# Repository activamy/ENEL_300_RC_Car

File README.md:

# ENEL_300_RC_Car
ENEL 300 Design Project 2026

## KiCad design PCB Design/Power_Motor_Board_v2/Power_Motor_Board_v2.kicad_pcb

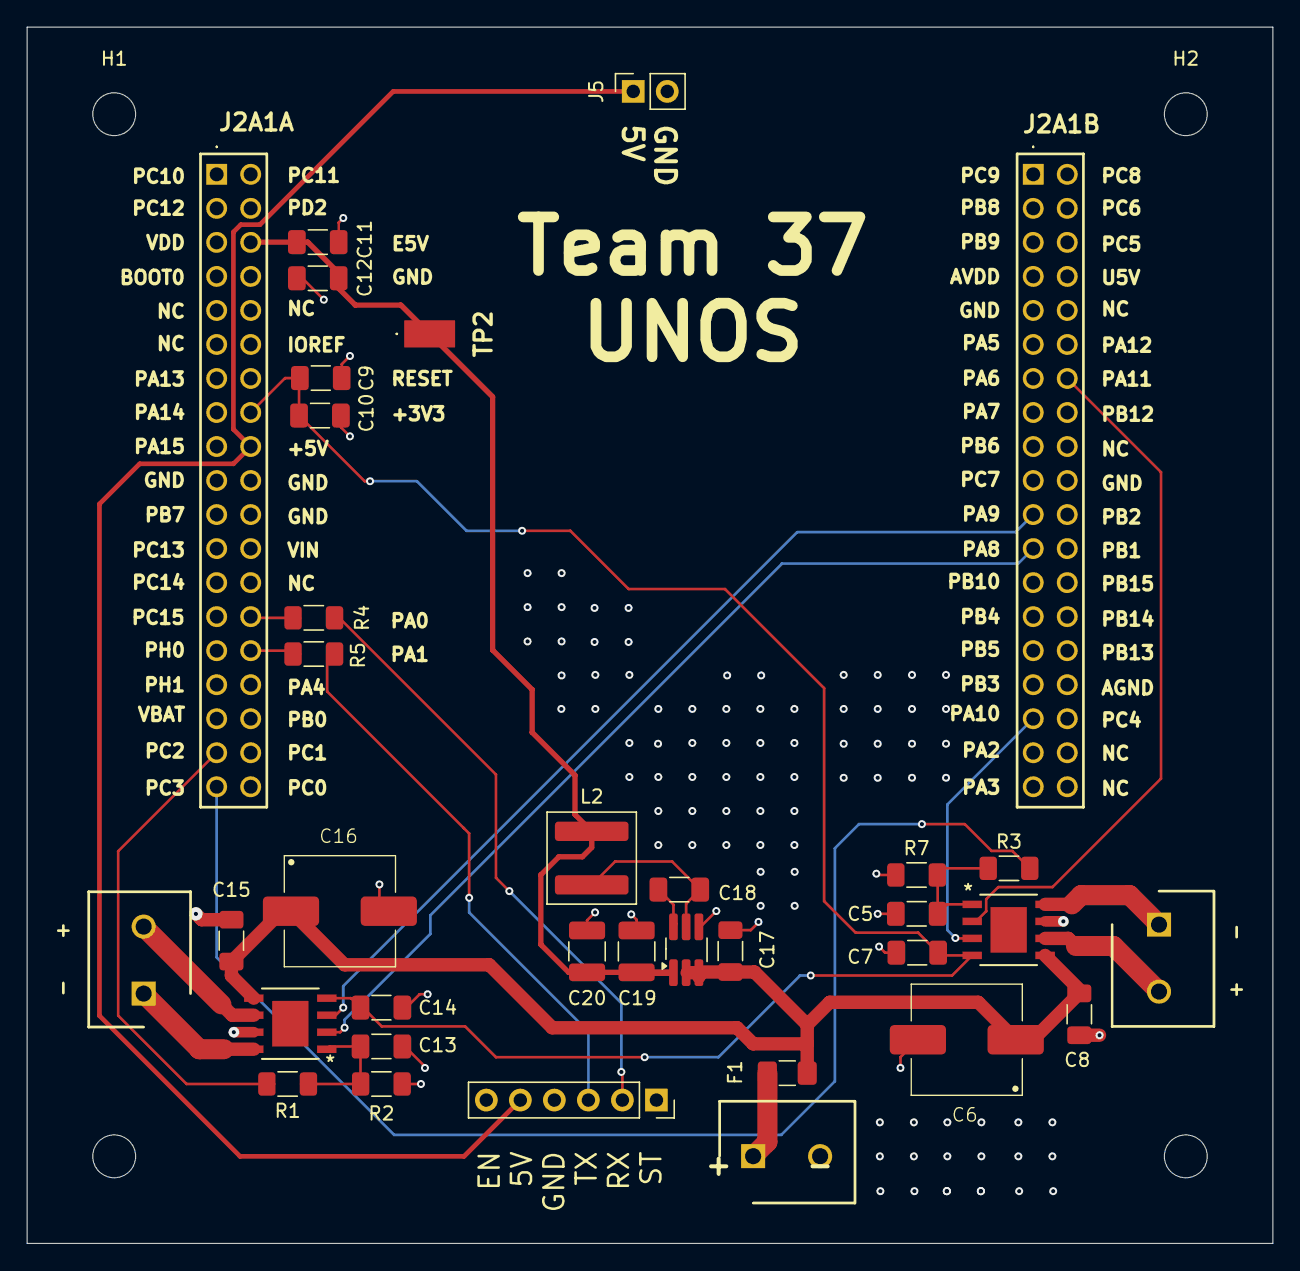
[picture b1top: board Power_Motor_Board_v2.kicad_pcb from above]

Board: 2 copper layers, 93.0 x 90.8 mm, 38 parts (0 on the bottom side), 24 nets.

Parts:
C5, C13: 10nF; C_1206_3216Metric_Pad1.33x1.80mm_HandSolder
C6, C16: 180uF; A768KE187M1ELAE029
C7, C8, C9, C11, C14, C15, C18: 0.1uF; C_1206_3216Metric_Pad1.33x1.80mm_HandSolder
C10, C12: 1uF; C_1206_3216Metric_Pad1.33x1.80mm_HandSolder
C17: 10uF; C_1206_3216Metric_Pad1.33x1.80mm_HandSolder
C19, C20: 22uF; C_1210_3225Metric_Pad1.33x2.70mm_HandSolder
F1: 4A; Fuse_1206_3216Metric_Pad1.42x1.75mm_HandSolder
H1, H2, H3, H4: MountingHole; MountingHole_3.2mm_M3
IC1, IC3: DRV8251ADDAR; SOIC-8-DDA-DRV8231_TEX
IC4: AP63205WU-7; TSOT-23-6_HandSoldering
J1, J2, J3: 691137710002; SHDR2W70P0X500_1X2_1000X750X1150P
J2A1: SSW-119-01-T-D; STM_Nucleo_Morpho_x2_Footprint
J4: Conn_01x06; PinSocket_1x06_P2.54mm_Vertical
J5: Conn_01x02_Socket; PinSocket_1x02_P2.54mm_Vertical
L2: 4.7uH; L_Wuerth_XHMI-6060
R1, R3, R4, R5: 0Ω; R_1206_3216Metric_Pad1.30x1.75mm_HandSolder
R2, R7: 750Ω; R_1206_3216Metric_Pad1.30x1.75mm_HandSolder
TP2: 5019

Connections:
5V_out: J2A1.A18 (+5V), J4.5, J5.1
+3V3: C7.1, C9.1, C10.1, C14.1, IC1.4 (VREF), IC3.4 (VREF), J2A1.A16 (+3V3)
+5V: C11.1, C12.1, C19.2, C20.2, IC4.1 (FB), J2A1.A6 (E5V), L2.2, TP2.1
+Vbatt: C6.1, C8.1, C15.1, C16.1, C17.1, F1.2, IC1.5 (VM), IC3.5 (VM), IC4.2 (EN), IC4.3 (VIN)
/+OUT_1: IC1.6 (OUT1), J3.2
/+OUT_2: IC3.6 (OUT1), J2.2
/-OUT_1: IC1.8 (OUT2), J3.1
/-OUT_2: IC3.8 (OUT2), J2.1
/BT_RX: J2A1.A28 (PA0), R4.1
/BT_TX: J2A1.A30 (PA1), R5.1
/IN1_MTR1: IC1.3 (IN1), J2A1.B21 (PA9)
/IN1_MTR2: IC3.3 (IN1), J2A1.B33 (PA10)
/IN2-MTR1: IC1.2 (IN2), J2A1.B23 (PA8)
/IN2_MTR2: IC3.2 (IN2), J2A1.B14 (PA11)
/I_MTR1: J2A1.A35 (PC2), R1.1
/I_MTR2: J2A1.A37 (PC3), R3.1
GND: C5.2, C6.2, C7.2, C8.2, C9.2, C10.2, C11.2, C12.2, C13.2, C14.2, C15.2, C16.2, C17.2, C19.1, C20.1, IC1.7 (GND_1), IC3.7 (GND_1), IC4.4 (GND), J1.2, J2A1.A8 (GND), J2A1.A19 (GND), J2A1.A20 (GND), J2A1.A22 (GND), J2A1.B9 (GND), J2A1.B20 (GND), J4.4, J5.2, R2.2, R7.2
unnamed: F1.1, J1.1
unnamed: C13.1, IC1.1 (IPROPI), R1.2, R2.1
unnamed: C5.1, IC3.1 (IPROPI), R3.2, R7.1
unnamed: C18.2, IC4.6 (BST)
unnamed: C18.1, IC4.5 (SW), L2.1
unnamed: J4.2, R4.2
unnamed: J4.3, R5.2

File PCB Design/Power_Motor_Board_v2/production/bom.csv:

Designator,Footprint,Quantity,Value,LCSC Part #
"C10, C12",1206,2,1uF,
"C11, C14, C15, C18, C7, C8, C9",1206,7,0.1uF,
"C13, C5",1206,2,10nF,
"C16, C6",A768KE187M1ELAE029,2,180uF,
C17,1206,1,10uF,
"C19, C20",1210,2,22uF,
F1,1206,1,4A,
"IC1, IC3",SOIC-8-DDA-DRV8231_TEX,2,DRV8251ADDAR,
IC4,TSOT-23-6_HandSoldering,1,AP63205WU-7,
J2A1,STM_Nucleo_Morpho_x2_Footprint,1,SSW-119-01-T-D,
J4,PinSocket_1x06_P2.54mm_Vertical,1,Conn_01x06,
J5,PinSocket_1x02_P2.54mm_Vertical,1,Conn_01x02_Socket,
L2,L_Wuerth_XHMI-6060,1,4.7uH,
"R1, R3, R4, R5",1206,4,0Ω,
"R2, R7",1206,2,750Ω,

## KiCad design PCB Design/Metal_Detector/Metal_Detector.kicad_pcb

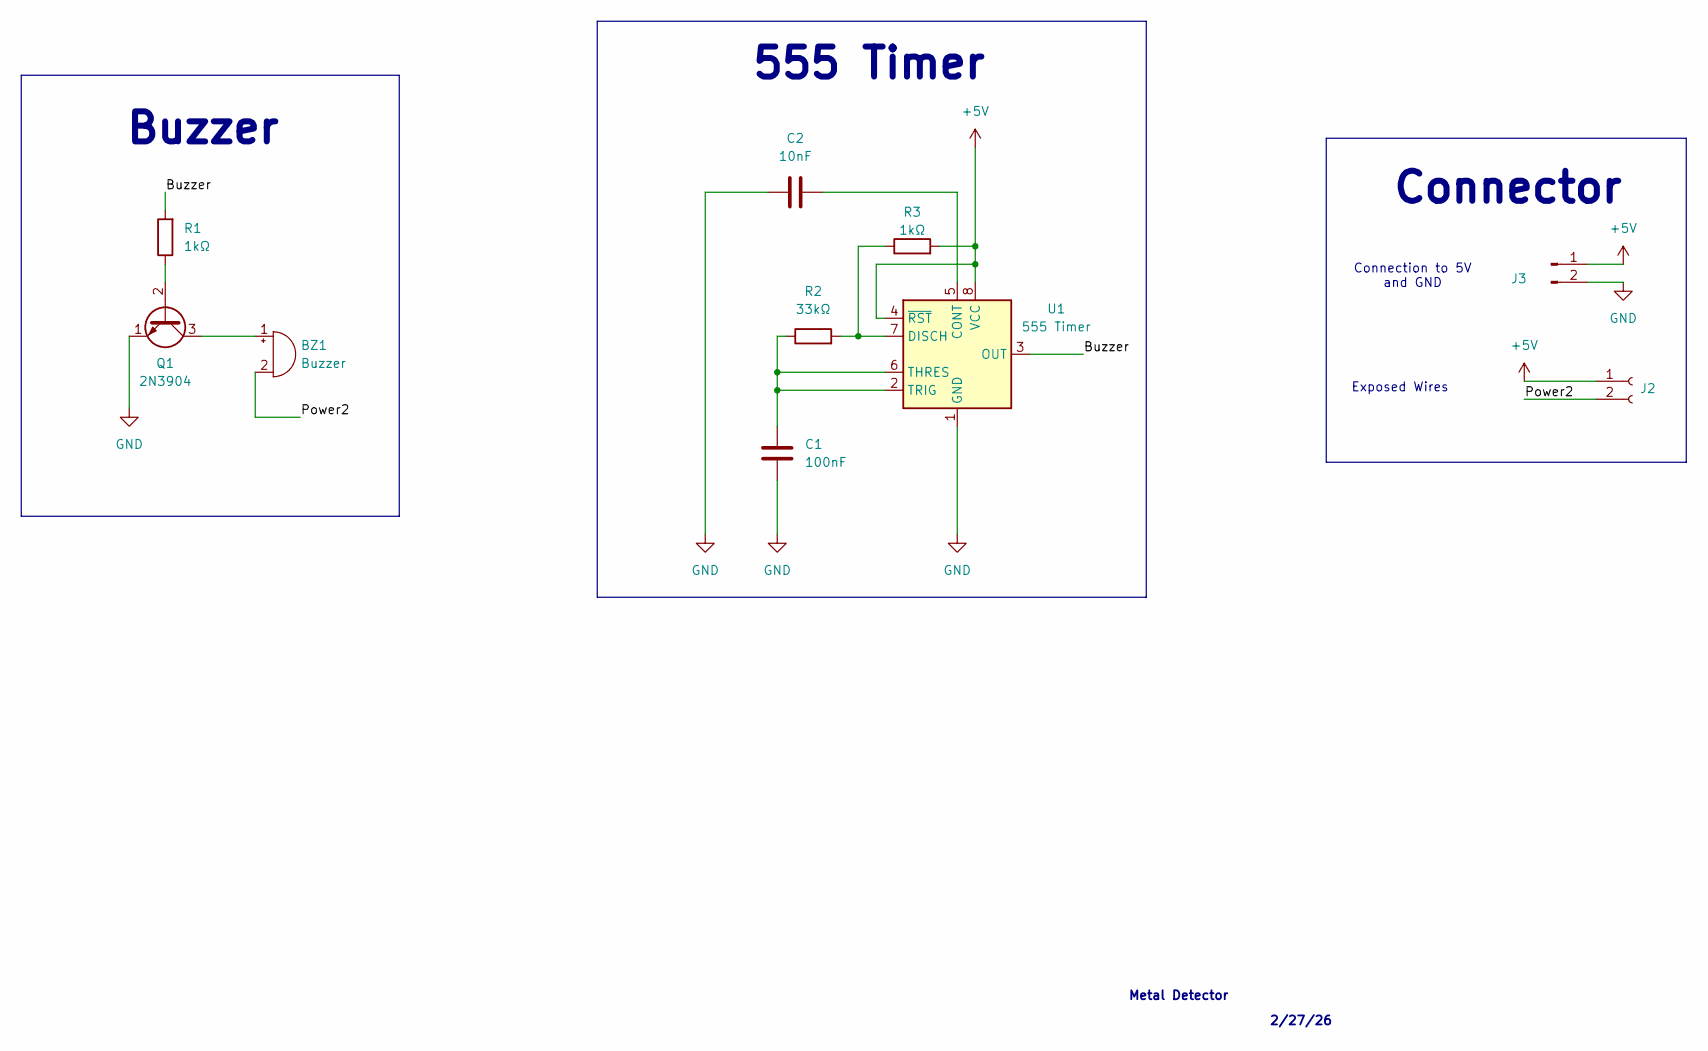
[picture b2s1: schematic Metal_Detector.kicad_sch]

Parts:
BZ1: Buzzer; Buzzer_12x9.5RM7.6
C1: 100nF; C_0805_2012Metric_Pad1.18x1.45mm_HandSolder
C2: 10nF; C_1206_3216Metric_Pad1.33x1.80mm_HandSolder
J2: Conn_01x02_Socket; PinSocket_1x02_P2.54mm_Vertical
J3: Conn_01x02_Pin; PinHeader_1x02_P2.54mm_Vertical
Q1: 2N3904; TO-92L_Inline
R1, R3: 1kΩ; R_1206_3216Metric_Pad1.30x1.75mm_HandSolder
R2: 33kΩ; R_1206_3216Metric_Pad1.30x1.75mm_HandSolder
U1: 555 Timer; SOIC-8_3.9x4.9mm_P1.27mm

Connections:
+5V: J2.1, J3.1, R3.2, U1.4 (~RST), U1.8 (VCC)
/Buzzer: R1.2, U1.3 (OUT)
/Power2: BZ1.2 (-), J2.2
GND: C1.2, C2.1, J3.2, Q1.1 (E), U1.1 (GND)
unnamed: BZ1.1 (+), Q1.3 (C)
unnamed: Q1.2 (B), R1.1
unnamed: C2.2, U1.5 (CONT)
unnamed: R2.2, R3.1, U1.7 (DISCH)
unnamed: C1.1, R2.1, U1.2 (TRIG), U1.6 (THRES)

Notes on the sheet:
Connector
Metal Detector
Buzzer
555 Timer
Exposed Wires
2/27/26
Connection to 5V and GND

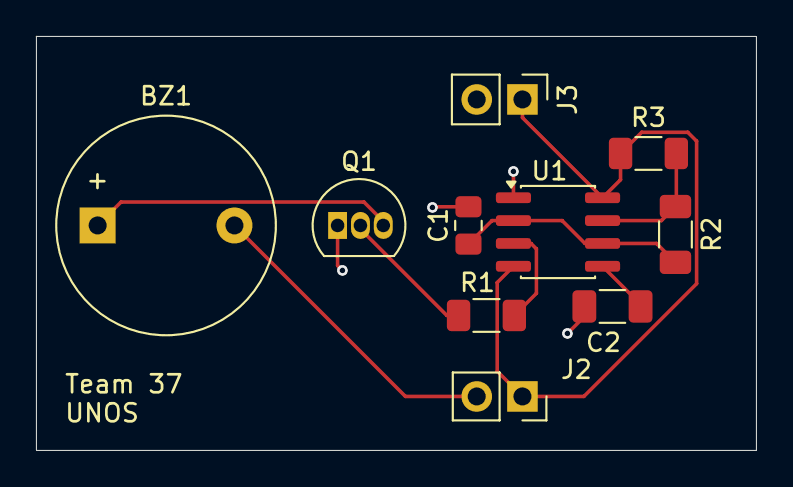
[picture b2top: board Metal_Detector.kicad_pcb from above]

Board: 2 copper layers, 40.0 x 23.0 mm, 10 parts (0 on the bottom side), 9 nets.

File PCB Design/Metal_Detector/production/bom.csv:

Designator,Footprint,Quantity,Value,LCSC Part #
C1,0805,1,100nF,
C2,1206,1,10nF,
"R1, R3",1206,2,1kΩ,
R2,1206,1,33kΩ,

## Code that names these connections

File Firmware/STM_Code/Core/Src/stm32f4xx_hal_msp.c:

/* USER CODE BEGIN Header */
/**
  ******************************************************************************
  * @file         stm32f4xx_hal_msp.c
  * @brief        This file provides code for the MSP Initialization
  *               and de-Initialization codes.
  ******************************************************************************
  * @attention
  *
  * Copyright (c) 2026 STMicroelectronics.
  * All rights reserved.
  *
  * This software is licensed under terms that can be found in the LICENSE file
  * in the root directory of this software component.
  * If no LICENSE file comes with this software, it is provided AS-IS.
  *
  ******************************************************************************
  */
/* USER CODE END Header */

/* Includes ------------------------------------------------------------------*/
#include "main.h"
/* USER CODE BEGIN Includes */

/* USER CODE END Includes */

/* Private typedef -----------------------------------------------------------*/
/* USER CODE BEGIN TD */

/* USER CODE END TD */

/* Private define ------------------------------------------------------------*/
/* USER CODE BEGIN Define */

/* USER CODE END Define */

/* Private macro -------------------------------------------------------------*/
/* USER CODE BEGIN Macro */

/* USER CODE END Macro */

/* Private variables ---------------------------------------------------------*/
/* USER CODE BEGIN PV */

/* USER CODE END PV */

/* Private function prototypes -----------------------------------------------*/
/* USER CODE BEGIN PFP */

/* USER CODE END PFP */

/* External functions --------------------------------------------------------*/
/* USER CODE BEGIN ExternalFunctions */

/* USER CODE END ExternalFunctions */

/* USER CODE BEGIN 0 */

/* USER CODE END 0 */

void HAL_TIM_MspPostInit(TIM_HandleTypeDef *htim);
                    /**
  * Initializes the Global MSP.
  */
void HAL_MspInit(void)
{

  /* USER CODE BEGIN MspInit 0 */

  /* USER CODE END MspInit 0 */

  __HAL_RCC_SYSCFG_CLK_ENABLE();
  __HAL_RCC_PWR_CLK_ENABLE();

  HAL_NVIC_SetPriorityGrouping(NVIC_PRIORITYGROUP_0);

  /* System interrupt init*/

  /* USER CODE BEGIN MspInit 1 */

  /* USER CODE END MspInit 1 */
}

/**
  * @brief ADC MSP Initialization
  * This function configures the hardware resources used in this example
  * @param hadc: ADC handle pointer
  * @retval None
  */
void HAL_ADC_MspInit(ADC_HandleTypeDef* hadc)
{
  GPIO_InitTypeDef GPIO_InitStruct = {0};
  if(hadc->Instance==ADC1)
  {
    /* USER CODE BEGIN ADC1_MspInit 0 */

    /* USER CODE END ADC1_MspInit 0 */
    /* Peripheral clock enable */
    __HAL_RCC_ADC1_CLK_ENABLE();

    __HAL_RCC_GPIOC_CLK_ENABLE();
    /**ADC1 GPIO Configuration
    PC2     ------> ADC1_IN12
    PC3     ------> ADC1_IN13
    */
    GPIO_InitStruct.Pin = GPIO_PIN_2|GPIO_PIN_3;
    GPIO_InitStruct.Mode = GPIO_MODE_ANALOG;
    GPIO_InitStruct.Pull = GPIO_NOPULL;
    HAL_GPIO_Init(GPIOC, &GPIO_InitStruct);

    /* USER CODE BEGIN ADC1_MspInit 1 */

    /* USER CODE END ADC1_MspInit 1 */

  }

}

/**
  * @brief ADC MSP De-Initialization
  * This function freeze the hardware resources used in this example
  * @param hadc: ADC handle pointer
  * @retval None
  */
void HAL_ADC_MspDeInit(ADC_HandleTypeDef* hadc)
{
  if(hadc->Instance==ADC1)
  {
    /* USER CODE BEGIN ADC1_MspDeInit 0 */

    /* USER CODE END ADC1_MspDeInit 0 */
    /* Peripheral clock disable */
    __HAL_RCC_ADC1_CLK_DISABLE();

    /**ADC1 GPIO Configuration
    PC2     ------> ADC1_IN12
    PC3     ------> ADC1_IN13
    */
    HAL_GPIO_DeInit(GPIOC, GPIO_PIN_2|GPIO_PIN_3);

    /* USER CODE BEGIN ADC1_MspDeInit 1 */

    /* USER CODE END ADC1_MspDeInit 1 */
  }

}

/**
  * @brief TIM_PWM MSP Initialization
  * This function configures the hardware resources used in this example
  * @param htim_pwm: TIM_PWM handle pointer
  * @retval None
  */
void HAL_TIM_PWM_MspInit(TIM_HandleTypeDef* htim_pwm)
{
  if(htim_pwm->Instance==TIM1)
  {
    /* USER CODE BEGIN TIM1_MspInit 0 */

    /* USER CODE END TIM1_MspInit 0 */
    /* Peripheral clock enable */
    __HAL_RCC_TIM1_CLK_ENABLE();
    /* USER CODE BEGIN TIM1_MspInit 1 */

    /* USER CODE END TIM1_MspInit 1 */

  }

}

void HAL_TIM_MspPostInit(TIM_HandleTypeDef* htim)
{
  GPIO_InitTypeDef GPIO_InitStruct = {0};
  if(htim->Instance==TIM1)
  {
    /* USER CODE BEGIN TIM1_MspPostInit 0 */

    /* USER CODE END TIM1_MspPostInit 0 */

    __HAL_RCC_GPIOA_CLK_ENABLE();
    /**TIM1 GPIO Configuration
    PA8     ------> TIM1_CH1
    PA9     ------> TIM1_CH2
    PA10     ------> TIM1_CH3
    PA11     ------> TIM1_CH4
    */
    GPIO_InitStruct.Pin = GPIO_PIN_8|GPIO_PIN_9|GPIO_PIN_10|GPIO_PIN_11;
    GPIO_InitStruct.Mode = GPIO_MODE_AF_PP;
    GPIO_InitStruct.Pull = GPIO_NOPULL;
    GPIO_InitStruct.Speed = GPIO_SPEED_FREQ_LOW;
    GPIO_InitStruct.Alternate = GPIO_AF1_TIM1;
    HAL_GPIO_Init(GPIOA, &GPIO_InitStruct);

    /* USER CODE BEGIN TIM1_MspPostInit 1 */

    /* USER CODE END TIM1_MspPostInit 1 */
  }

}
/**
  * @brief TIM_PWM MSP De-Initialization
  * This function freeze the hardware resources used in this example
  * @param htim_pwm: TIM_PWM handle pointer
  * @retval None
  */
void HAL_TIM_PWM_MspDeInit(TIM_HandleTypeDef* htim_pwm)
{
  if(htim_pwm->Instance==TIM1)
  {
    /* USER CODE BEGIN TIM1_MspDeInit 0 */

    /* USER CODE END TIM1_MspDeInit 0 */
    /* Peripheral clock disable */
    __HAL_RCC_TIM1_CLK_DISABLE();
    /* USER CODE BEGIN TIM1_MspDeInit 1 */

    /* USER CODE END TIM1_MspDeInit 1 */
  }

}

/**
  * @brief UART MSP Initialization
  * This function configures the hardware resources used in this example
  * @param huart: UART handle pointer
  * @retval None
  */
void HAL_UART_MspInit(UART_HandleTypeDef* huart)
{
  GPIO_InitTypeDef GPIO_InitStruct = {0};
  if(huart->Instance==UART4)
  {
    /* USER CODE BEGIN UART4_MspInit 0 */

    /* USER CODE END UART4_MspInit 0 */
    /* Peripheral clock enable */
    __HAL_RCC_UART4_CLK_ENABLE();

    __HAL_RCC_GPIOA_CLK_ENABLE();
    /**UART4 GPIO Configuration
    PA0-WKUP     ------> UART4_TX
    PA1     ------> UART4_RX
    */
    GPIO_InitStruct.Pin = GPIO_PIN_0|GPIO_PIN_1;
    GPIO_InitStruct.Mode = GPIO_MODE_AF_PP;
    GPIO_InitStruct.Pull = GPIO_NOPULL;
    GPIO_InitStruct.Speed = GPIO_SPEED_FREQ_VERY_HIGH;
    GPIO_InitStruct.Alternate = GPIO_AF8_UART4;
    HAL_GPIO_Init(GPIOA, &GPIO_InitStruct);

    /* USER CODE BEGIN UART4_MspInit 1 */

    /* USER CODE END UART4_MspInit 1 */
  }
  else if(huart->Instance==USART2)
  {
    /* USER CODE BEGIN USART2_MspInit 0 */

    /* USER CODE END USART2_MspInit 0 */
    /* Peripheral clock enable */
    __HAL_RCC_USART2_CLK_ENABLE();

    __HAL_RCC_GPIOA_CLK_ENABLE();
    /**USART2 GPIO Configuration
    PA2     ------> USART2_TX
    PA3     ------> USART2_RX
    */
    GPIO_InitStruct.Pin = USART_TX_Pin|USART_RX_Pin;
    GPIO_InitStruct.Mode = GPIO_MODE_AF_PP;
    GPIO_InitStruct.Pull = GPIO_NOPULL;
    GPIO_InitStruct.Speed = GPIO_SPEED_FREQ_VERY_HIGH;
    GPIO_InitStruct.Alternate = GPIO_AF7_USART2;
    HAL_GPIO_Init(GPIOA, &GPIO_InitStruct);

    /* USER CODE BEGIN USART2_MspInit 1 */

    /* USER CODE END USART2_MspInit 1 */
  }

}

/**
  * @brief UART MSP De-Initialization
  * This function freeze the hardware resources used in this example
  * @param huart: UART handle pointer
  * @retval None
  */
void HAL_UART_MspDeInit(UART_HandleTypeDef* huart)
{
  if(huart->Instance==UART4)
  {
    /* USER CODE BEGIN UART4_MspDeInit 0 */

    /* USER CODE END UART4_MspDeInit 0 */
    /* Peripheral clock disable */
    __HAL_RCC_UART4_CLK_DISABLE();

    /**UART4 GPIO Configuration
    PA0-WKUP     ------> UART4_TX
    PA1     ------> UART4_RX
    */
    HAL_GPIO_DeInit(GPIOA, GPIO_PIN_0|GPIO_PIN_1);

    /* USER CODE BEGIN UART4_MspDeInit 1 */

    /* USER CODE END UART4_MspDeInit 1 */
  }
  else if(huart->Instance==USART2)
  {
    /* USER CODE BEGIN USART2_MspDeInit 0 */

    /* USER CODE END USART2_MspDeInit 0 */
    /* Peripheral clock disable */
    __HAL_RCC_USART2_CLK_DISABLE();

    /**USART2 GPIO Configuration
    PA2     ------> USART2_TX
    PA3     ------> USART2_RX
    */
    HAL_GPIO_DeInit(GPIOA, USART_TX_Pin|USART_RX_Pin);

    /* USER CODE BEGIN USART2_MspDeInit 1 */

    /* USER CODE END USART2_MspDeInit 1 */
  }

}

/* USER CODE BEGIN 1 */

/* USER CODE END 1 */

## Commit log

2026-02-09 Transfers v1 of motor schematic
2026-02-09 Majority of schematic built
    Bluetooth module part left to build
2026-02-10 Completed Schematic
2026-02-11 Rough draft of the layout is completed
2026-02-11 layout organized
2026-02-11 layout organized commit part 2
2026-02-14 First Revision of Power_Motor PCB
2026-02-20 Created STM Folder for coding purposes
2026-02-20 Moved the main code files into its own folder
    allows other folders to be made for specific test parts for other people's branches
2026-02-20 undid folder moving bc im funny :P
2026-02-20 Moved main code into a firmware folder too
2026-02-21 Added a test project for the headlights
    Goal is to use a phone to turn on an led via bluetooth using the UART4 line of the nucleo board as well as to learn more about bluetooth
    Is it working? no
2026-02-25 Created a BOM file
2026-02-26 Started assigning Manufacture Part Numbers
2026-02-27 Finished assigning part numbers
2026-02-27 Finished BOM list and updated layout to use the correct 180uF capacitor footprint
2026-02-27 Started v2 of main board
    Got rid of 5V buck for motor driver, driver now powered by battery, added a metal detector connector, added 0Ω to tx/rx lines in case we want to use another line
2026-02-28 made a metal detector folder!
    :)
2026-02-28 made the metal detector schematic with the amazingamy
2026-02-28 added connector for voltage? thingy (5V + GND)
2026-02-28 personal notes for future, and changes to the schmatic
    i forgot my changes icl. idk if i mentioned adding the metal detector connector pins that connect to 5V and GND
2026-03-01 did all the footprints w amy chan
2026-03-01 did layout and traces w amy exported step file
2026-03-01 Start v2 of main board layout
2026-03-02 Continued board layout and mesurements as well as edited BOM
2026-03-03 traced out the layout
2026-03-03 Added new mx/ide project for headlights
2026-03-03 Added new mx/ide project for headlights and deleted previous one
    onboard led ld2 turns on and off based on buttons
2026-03-04 changes made bc i tested with a diff board?????
2026-03-04 changed ouput led to a green led on beadboard
    success
2026-03-04 Add README for Bluetooth controller test code
2026-03-04 Changed toggles to be compatible with the SriTu Hobby Bluetooth Controller
    U turns on the led and L turns it off for the time being.
2026-03-04 added code to double check the uart4 connection
    in case commands dont run, use connection to ensure the line is working
2026-03-04 can i plz connect to a terminal im acc gonna lose it bro ;-;
    Things I learnt: you cannot print nor write thru stm :(, have to get sum weird code or smth and the ide doesnt have a terminal???? gotta download smth but i dont wanna :(
    but good news: just transmit it back to the serial terminal on phone :), tho I CANT DO THAT IF IM CONNECTED TO THE FRICKING CONTROLLER WTF DO I DO MAN
2026-03-04 Brought back the notes i accidentally deleted and changed the transmit location
    good news!!!!! i can just change the transmit to just go to my laptop instead!!!! I have this thing called RealTerm, and i just gotta connect to the port and see it happen in real time woahhhhhhhhhhh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
    now i just gotta figure out the things for this controller so i can configure thingies
2026-03-04 Create Controller_Notes.md
    Created notes on the bluetooth controller and initial plannings for controller
2026-03-04 Created RC Controller stuff
2026-03-04 initialized app i think idk
2026-03-04 restarted bc things didnt save properly or smth idk
2026-03-04 created it frfr i swear
2026-03-04 edited some files
2026-03-07 initial working ultrasonic sensor code
2026-03-08 idk what the firmware things are but slay ig and idk what i changed in the pcb either
    /gen what did I do and why did i do
2026-03-11 gerber file
    goofy goober
2026-03-11 changed to v2 main board
2026-03-11 smth
2026-03-12 fixed board, gerber bs, ummmmm and idk its also 1am and i have to wake at 6am ;-;
2026-03-13 changed smth and ig made the step file for v2 of the pcb design oh and production files too
2026-03-13 Updated readme in firmware
2026-03-14 idk what these changes are but they exist
2026-03-14 add filter. it works!
2026-03-14 moved ultrasonic code to firmware folder
2026-03-15 WHAT DID I CHANGE????????
2026-03-15 added folder with new code with added lcd screen implementation
2026-03-15 Reduce filter size for distance measurement (10-->5)
2026-03-15 ermmmmmm all i did was add more notes...... so wtf are these files 😨
2026-03-15 changed letters
2026-03-15 got rid of the useless folders and added app
    but no one can see the app >:)
2026-03-16 added motor code
    for motor 2. using pa11 and gpio pb4 and pb5
2026-03-16 ermmmmm ten thousand unknown changes, but implemented a switch/case function for the data received through bluetooth,
    all that's left is to implement motor code and test!
2026-03-17 idk what the changes to bluetooth were
2026-03-17 add new motor code with header file
2026-03-17 added motor code to bluetooth
2026-03-17 fixed some main.c bluetooth motor speed code
2026-03-18 working motor to controller connection!!!!!!!!
2026-03-18 adjusted cases motor functions
2026-03-30 integrated hcsr04+lcd with motor+hc-05
2026-03-30 initialize a micropython file for new bluetooth code
2026-03-31 working code....
2026-04-01 stashing changes, deleting old code after
2026-04-01 wifi code for controller plus it's html webpage
    self created wifi server thingy and a eebpage is the new controller
2026-04-04 current updated code
2026-04-08 ummmm i did smth?
2026-04-10 move motor command switch case out of infinite while (into rxcallback)
2026-04-10 fix button 'k' direction
2026-04-10 update uart to usart3, update and complete pcb motor code, turn on all motor gpio
2026-04-11 add tim2 for sensor stuff
2026-04-11 add set_motor_speed to forward in infinite-loop
2026-04-11 configured uart communication btwn pi and stm, it doesnt work properly :shrug
2026-04-12 test motor driver for forwards and the whatnots
2026-04-12 some changes idk what :P
2026-04-13 working iteration, hopefully the last iteration
2026-04-13 modify motor code and integrate ultrasonic/lcd code
2026-04-13 add stmUARTpico code to Bluetooth2light code
2026-04-13 integrate dataToMotor func with uart from pico
2026-04-13 changes saved b4 laptop crashed
2026-04-14 change speed settings and baud rate
2026-04-15 change max speed to 80
2026-04-15 final lmao
